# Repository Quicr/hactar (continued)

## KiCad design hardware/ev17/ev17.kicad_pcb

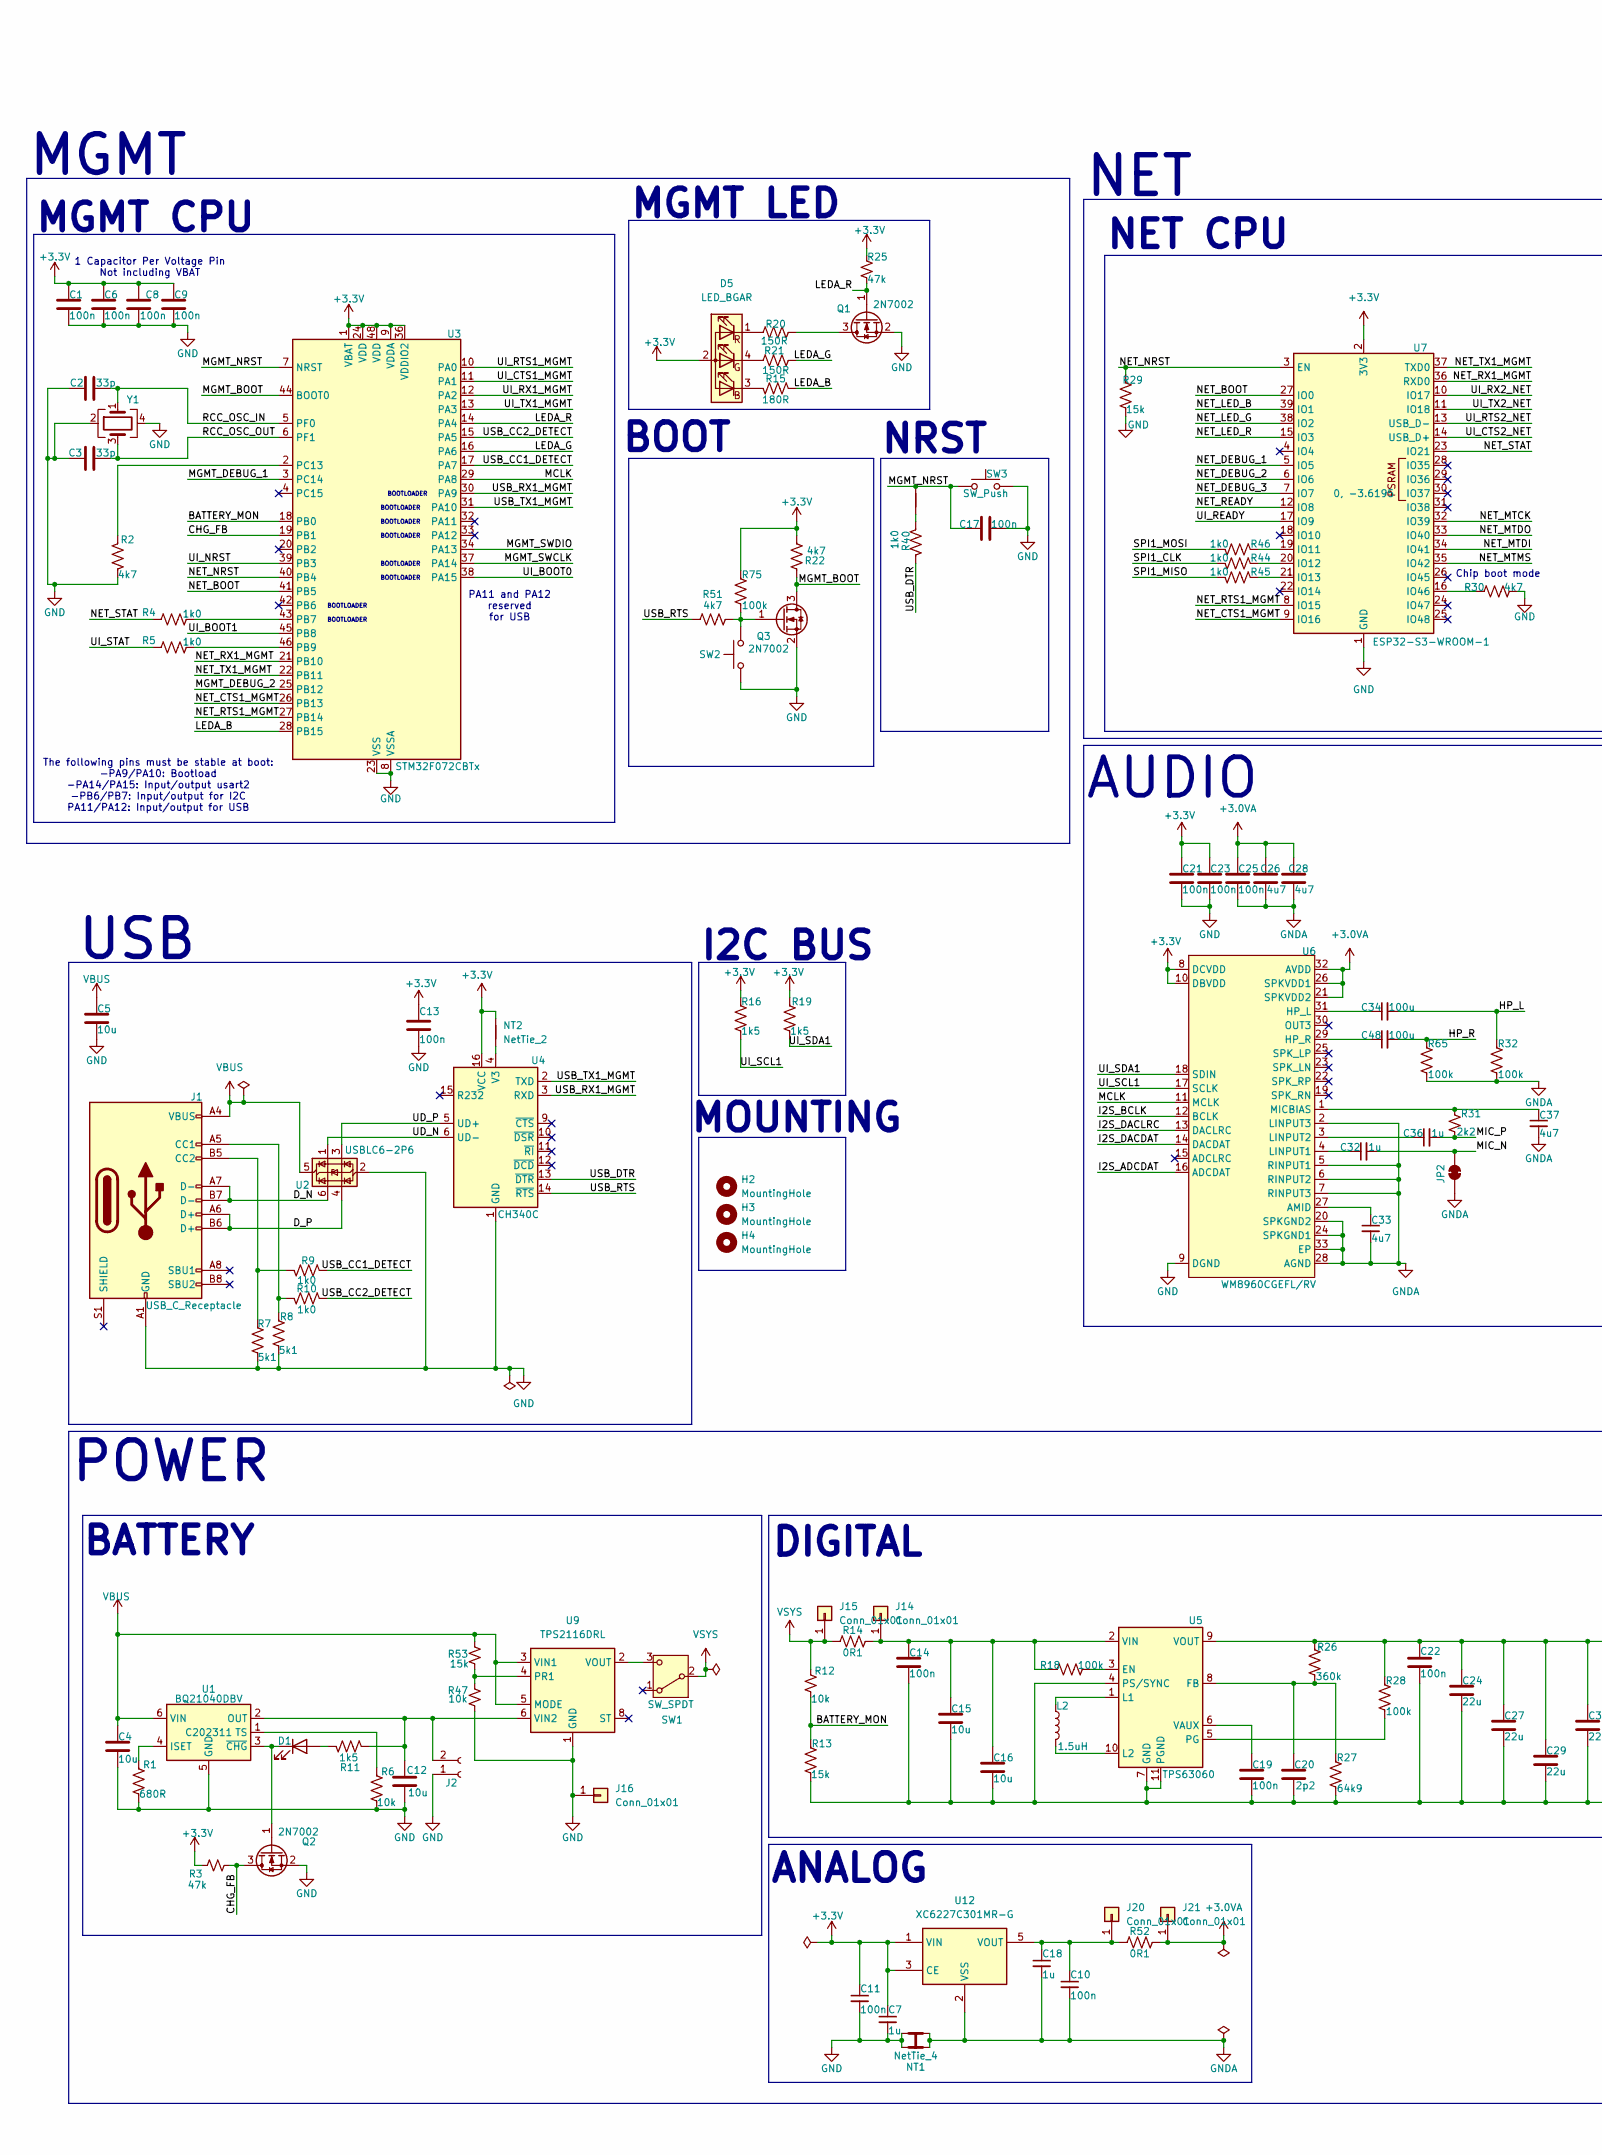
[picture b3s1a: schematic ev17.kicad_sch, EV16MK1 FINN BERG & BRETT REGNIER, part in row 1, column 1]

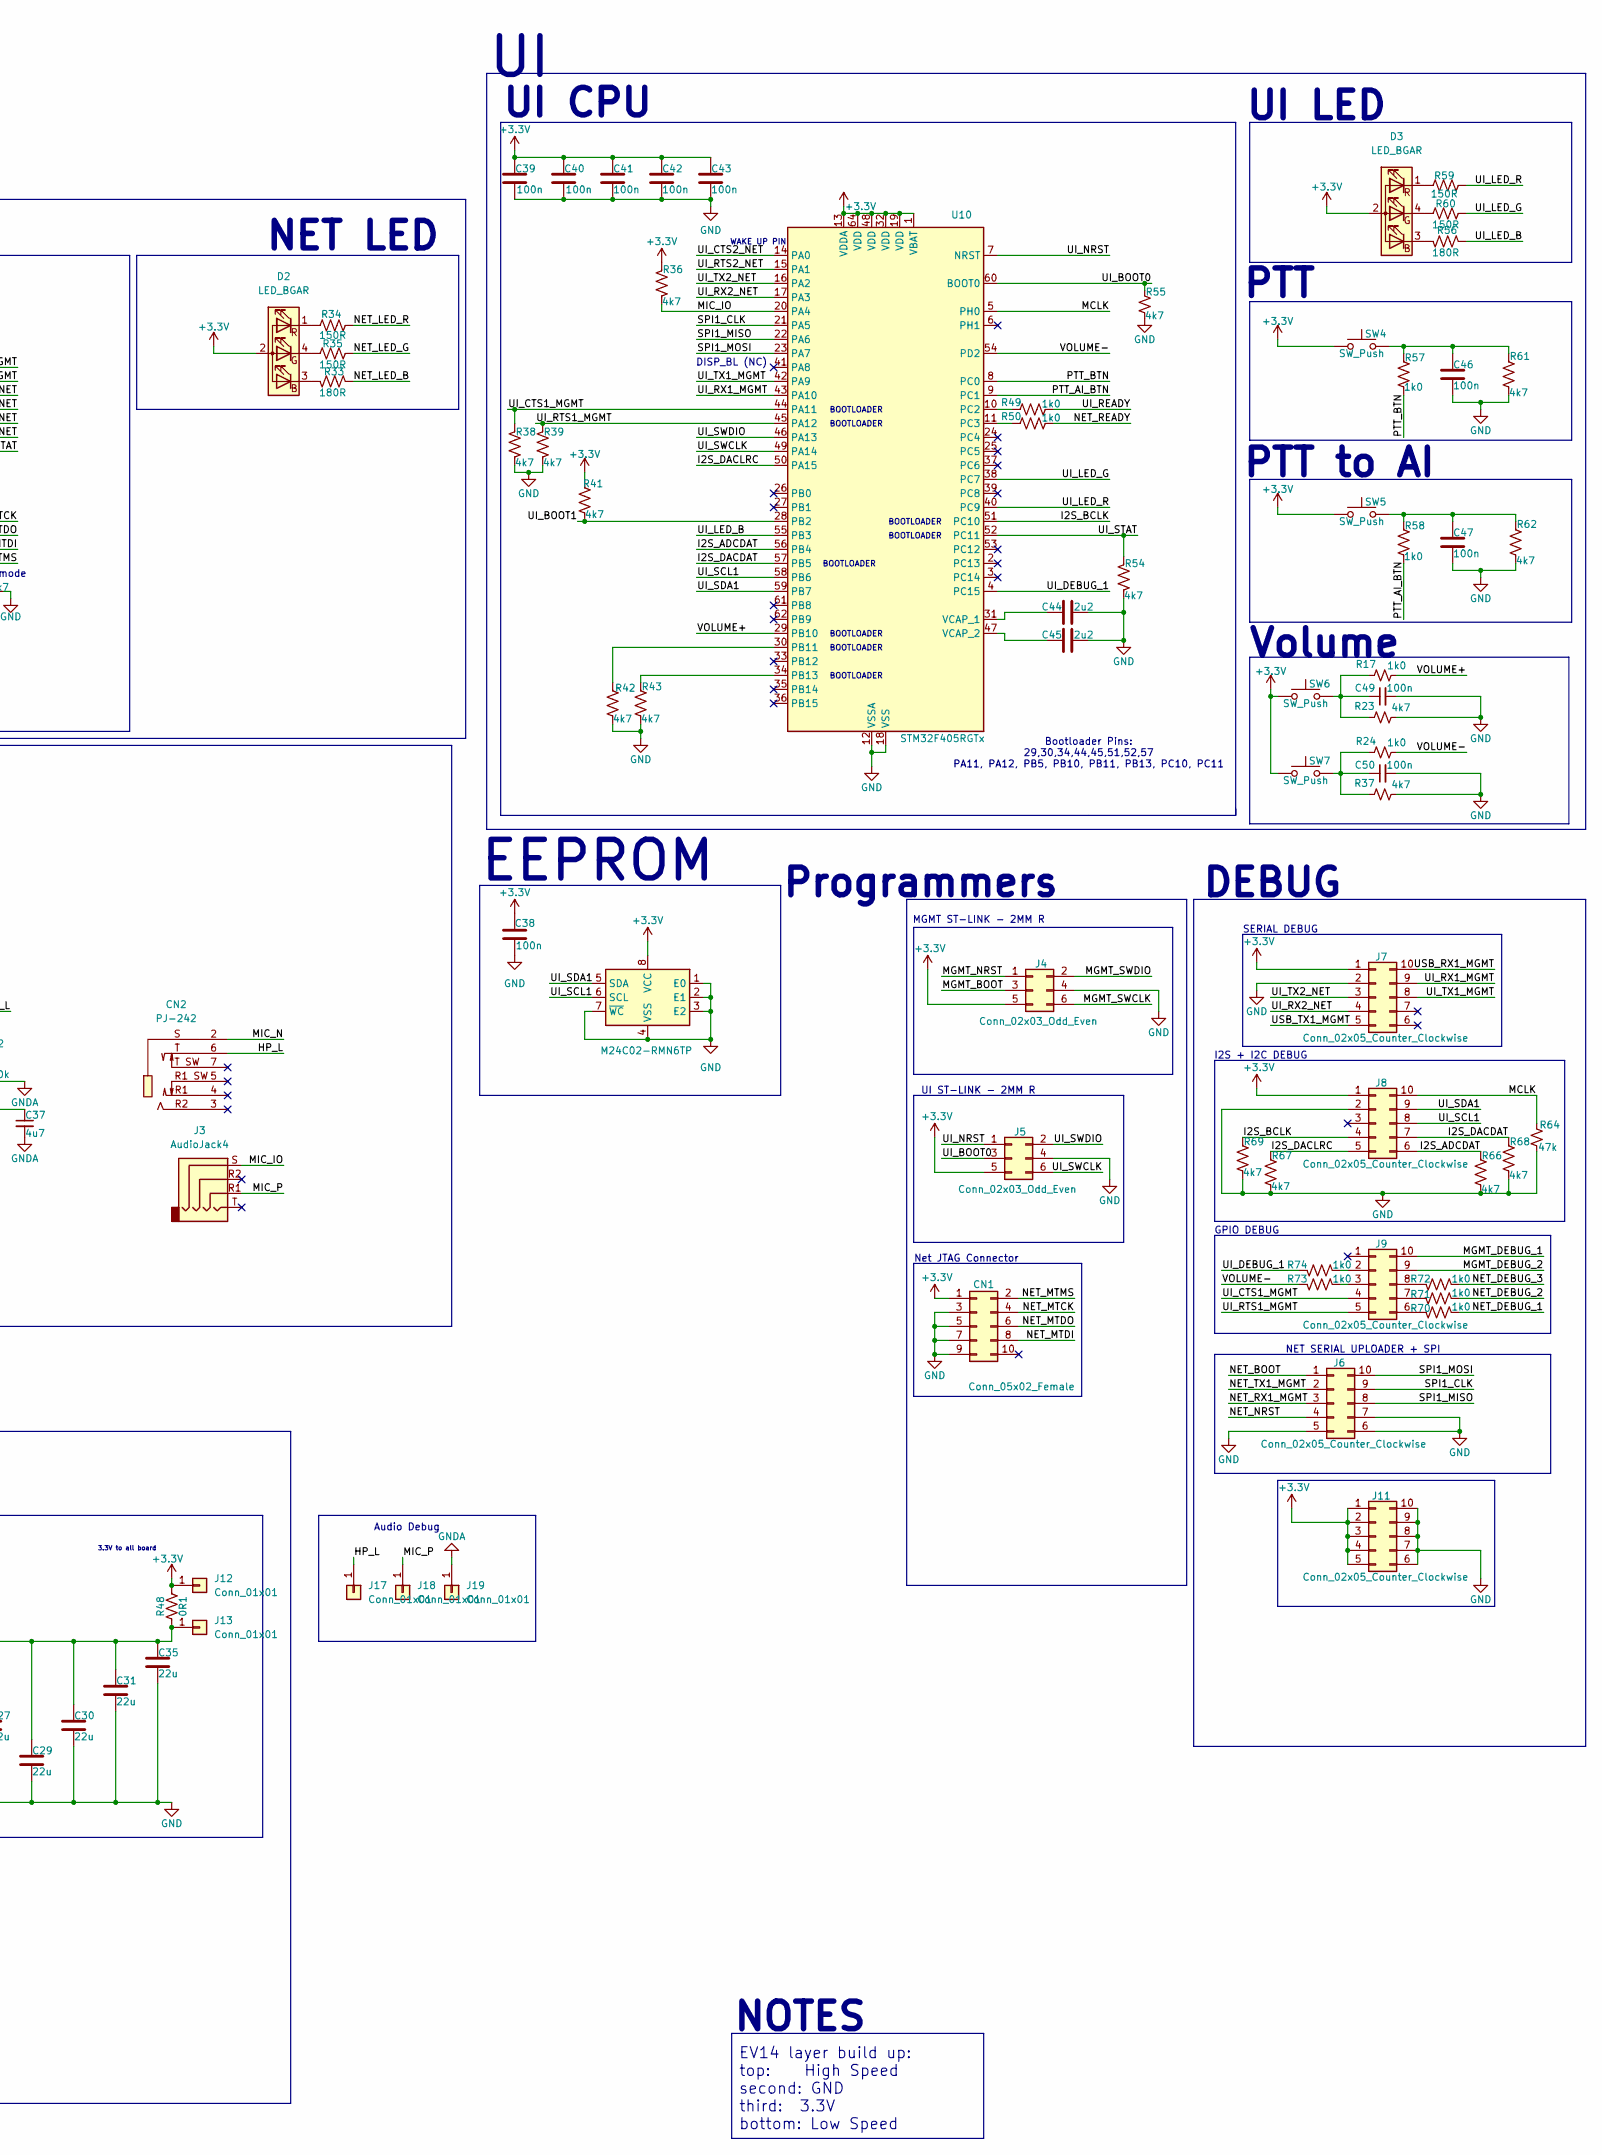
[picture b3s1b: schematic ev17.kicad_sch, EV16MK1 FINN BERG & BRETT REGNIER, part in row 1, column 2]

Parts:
C1, C6, C8, C9, C13, C17, C21, C23, C25, C38, C39, C40, C41, C42, C43, C46, C47, C49, C50: 100n; C_0402_1005Metric; JLCPCB Part # C1525
C2, C3: 33p; C_0805_2012Metric; JLCPCB Part # C107115
C4, C5, C12: 10u; C_0402_1005Metric; JLCPCB Part # C307415
C7, C18, C32, C36: 1u; C_0402_1005Metric; JLCPCB Part # C52923
C10, C11, C14, C19, C22: 100n; C_0805_2012Metric; JLCPCB Part # C85866
C15, C16: 10u; C_0805_2012Metric; JLCPCB Part # C17024
C20: 2p2; C_0805_2012Metric; JLCPCB Part # C519933
C24, C27, C29, C30, C31, C35: 22u; C_0805_2012Metric; JLCPCB Part # C5674
C26, C28, C33, C37: 4u7; C_0402_1005Metric; JLCPCB Part # C23733
C34, C48: 100u; C_1206_3216Metric; JLCPCB Part # C15008
C44, C45: 2u2; C_0402_1005Metric; JLCPCB Part # C12530
CN1: Conn_05x02_Female; IDC-SMD_10P-P1.27_X1270WVS-2X05B-6TV01; JLCPCB Part # C2962222
CN2: PJ-242; AUDIO-SMD_PJ-242D-SMT; JLCPCB Part # C431536
D1: LED; D_0805_2012Metric; JLCPCB Part # C130114
D2, D3, D5: LED_BGAR; LED-ARRAY-SMD_4P-L1.6-W1.5-TL_NH-B1515RGBA; JLCPCB Part # C2874115
H2, H3, H4: MountingHole; MountingHole_2.7mm_M2.5
J1: USB_C_Receptacle; USB-C_SMD-TYPE-C-31-M-12; JLCPCB Part # C165948
J2: Conn_01x02_Socket; JST_PH_S2B-PH-SM4-TB_1x02-1MP_P2.00mm_Horizontal; JLCPCB Part # C295747
J3: AudioJack4; AUDIO-SMD_PJ-320D; JLCPCB Part # C431535
J4, J5: Conn_02x03_Odd_Even; HDR-SMD_6P-P2.54-V-M-R2-C3-LS7.5-2; JLCPCB Part # C3294461
J6, J7, J8, J9, J11: Conn_02x05_Counter_Clockwise; HDR-SMD_10P-P2.54-V-F-R2-C5-LS7.1-1; JLCPCB Part # C3975150
J12, J13, J14, J15, J16, J17, J18, J19, J20, J21: Conn_01x01; PinSocket_1x01_P2.00mm_Vertical; JLCPCB Part # C2882984
JP2: SolderJumper_2_Bridged; NetTie-2_SMD_Pad0.5mm
L2: 1.5uH; L_Coilcraft_XxL4020; JLCPCB Part # C3033018
NT1: NetTie_4; NetTie-4_SMD_Pad0.5mm
NT2, NT3: NetTie_2; NetTie-2_SMD_Pad0.5mm
Q1, Q2, Q3: 2N7002; SOT-23; JLCPCB Part # C8545
R1: 680R; R_0402_1005Metric; JLCPCB Part # C25130
R2, R22, R23, R30, R36, R37, R38, R39, R41, R42, R43, R51, R54, R55, R61, R62, R66, R67, R68, R69: 4k7; R_0402_1005Metric; JLCPCB Part # C25900
R3, R25, R64: 47k; R_0402_1005Metric; JLCPCB Part # C25792
R4, R5, R9, R10, R17, R24, R40, R44, R45, R46, R49, R50, R57, R58, R70, R71, R72, R73, R74: 1k0; R_0402_1005Metric; JLCPCB Part # C11702
R6, R12, R47: 10k; R_0402_1005Metric; JLCPCB Part # C25744
R7, R8: 5k1; R_0402_1005Metric; JLCPCB Part # C25905
R11, R16, R19: 1k5; R_0402_1005Metric; JLCPCB Part # C25867
R13, R29, R53: 15k; R_0402_1005Metric; JLCPCB Part # C25756
R14, R48, R52: 0R1; R_0603_1608Metric; JLCPCB Part # C111027
R15, R33, R56: 180R; R_0402_1005Metric; JLCPCB Part # C25087
R18, R28, R32, R65, R75: 100k; R_0402_1005Metric; JLCPCB Part # C25741
R20, R21, R34, R35, R59, R60: 150R; R_0402_1005Metric; JLCPCB Part # C25082
R26: 360k; R_0402_1005Metric; JLCPCB Part # C45956
R27: 64k9; R_0402_1005Metric; JLCPCB Part # C26984
R31: 2k2; R_0402_1005Metric; JLCPCB Part # C25879
SW1: SW_SPDT; SW-TH_SS-12D11G5R; JLCPCB Part # C388633
SW2, SW3: SW_Push; KEY-SMD_4P-L4.2-W3.2-P2.20-LS4.6; JLCPCB Part # C139797
SW4, SW5: SW_Push; SW-SMD_4P-L5.1-W5.1-P3.70-LS6.5-TL_H1.5; JLCPCB Part # C318886
SW6, SW7: SW_Push; SW-SMD_SHOU_TS36CA-0.6; JLCPCB Part # C2906288
U1: BQ21040DBV; SOT-23-6; JLCPCB Part # C202311
U2: USBLC6-2P6; SOT-666; JLCPCB Part # C2827693
U3: STM32F072CBTx; LQFP-48_7x7mm_P0.5mm; JLCPCB Part # C80488
U4: CH340C; SOIC-16_3.9x9.9mm_P1.27mm; JLCPCB Part # C84681
U5: TPS63060; Texas_S-PWSON-N10_ThermalVias; JLCPCB Part # C48567
U6: WM8960CGEFL/RV; QFN-32-1EP_5x5mm_P0.5mm_EP3.45x3.45mm_ThermalVias; JLCPCB Part # C18752
U7: ESP32-S3-WROOM-1; JLCPCB Part # C2913204
U8: M24C02-RMN6TP; SOIC-8_3.9x4.9mm_P1.27mm; JLCPCB Part # C83836
U9: TPS2116DRL; SOT-583-8; JLCPCB Part # C3235557
U10: STM32F405RGTx; LQFP-64_10x10mm_P0.5mm; JLCPCB Part # C15742
U12: XC6227C301MR-G; SOT-23-5; JLCPCB Part # C484285
Y1: Crystal_GND24; Crystal_SMD_3225-4Pin_3.2x2.5mm; JLCPCB Part # C13738

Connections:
/Analog_Sense: C10.1, C18.1, J20.1, R52.1, U12.5 (VOUT); also elsewhere on the board
/BATTERY_MON: R12.1, R13.1, U3.18 (PB0)
/BB_Vin_Sense: C14.1, C15.1, C16.1, R14.2, R18.1, U5.2 (VIN); also elsewhere on the board
/BB_Vout_Sense: C22.1, C24.1, C27.1, C29.1, C30.1, C31.1, C35.1, R26.2, R28.2, R48.1, U5.9 (VOUT); also elsewhere on the board
/CHG_FB: Q2.3 (D), R3.1, U3.19 (PB1)
/D_N: J1.A7 (D-), J1.B7 (D-), U2.6 (I/O1)
/D_P: J1.A6 (D+), J1.B6 (D+), U2.4 (I/O2)
/HP_L: C34.2, CN2.6, J17.1, R32.2
/I2S_ADCDAT: J8.6, R66.1, U6.16 (ADCDAT), U10.56 (PB4)
/I2S_BCLK: J8.4, R69.1, U6.12 (BCLK), U10.51 (PC10)
/I2S_DACDAT: J8.7, R68.1, U6.14 (DACDAT), U10.57 (PB5)
/I2S_DACLRC: J8.5, R67.1, U6.13 (DACLRC), U10.50 (PA15)
/LEDA_B: R15.2, U3.28 (PB15)
/LEDA_G: R21.2, U3.16 (PA6)
/LEDA_R: Q1.1 (G), R25.1, U3.14 (PA4)
/MCLK: J8.10, R64.1, U3.29 (PA8), U6.11 (MCLK), U10.5 (PH0)
/MGMT_BOOT: J4.3, Q3.3 (D), R22.1, U3.44 (BOOT0)
/MGMT_DEBUG_1: J9.10, U3.3 (PC14)
/MGMT_DEBUG_2: J9.9, U3.25 (PB12)
/MGMT_NRST: C17.1, J4.1, NT3.2, SW3.1, SW3.2, U3.7 (NRST)
/MGMT_SWCLK: J4.6, U3.37 (PA14)
/MGMT_SWDIO: J4.2, U3.34 (PA13)
/MIC_N: C32.2, CN2.2, JP2.1 (A)
/MIC_P: C36.2, J3.R1, J18.1, R31.1
/NET_BOOT: J6.1, U3.41 (PB5), U7.27 (IO0)
/NET_CTS1_MGMT: U3.26 (PB13), U7.9 (IO16)
/NET_DEBUG_1: R70.1, U7.5 (IO5)
/NET_DEBUG_2: R71.1, U7.6 (IO6)
/NET_DEBUG_3: R72.1, U7.7 (IO7)
/NET_LED_B: R33.1, U7.39 (IO1)
/NET_LED_G: R35.1, U7.38 (IO2)
/NET_LED_R: R34.1, U7.15 (IO3)
/NET_MTCK: CN1.4, U7.32 (IO39)
/NET_MTDI: CN1.8, U7.34 (IO41)
/NET_MTDO: CN1.6, U7.33 (IO40)
/NET_MTMS: CN1.2, U7.35 (IO42)
/NET_NRST: J6.4, R29.1, U3.40 (PB4), U7.3 (EN)
/NET_READY: R50.1, U7.12 (IO8)
/NET_RTS1_MGMT: U3.27 (PB14), U7.8 (IO15)
/NET_RX1_MGMT: J6.3, U3.21 (PB10), U7.36 (RXD0)
/NET_STAT: R4.2, U7.23 (IO21)
/NET_TX1_MGMT: J6.2, U3.22 (PB11), U7.37 (TXD0)
/PTT_AI_BTN: R58.1, U10.9 (PC1)
/PTT_BTN: R57.1, U10.8 (PC0)
/RCC_OSC_IN: C2.2, U3.5 (PF0), Y1.1
/RCC_OSC_OUT: C3.2, U3.6 (PF1), Y1.3
/SPI1_CLK: J6.9, R44.1, U10.21 (PA5)
/SPI1_MISO: J6.8, R45.1, U10.22 (PA6)
/SPI1_MOSI: J6.10, R46.1, U10.23 (PA7)
/UD_N: U2.1 (I/O1), U4.6 (UD-)
/UD_P: U2.3 (I/O2), U4.5 (UD+)
/UI_BOOT0: J5.3, R55.1, U3.38 (PA15), U10.60 (BOOT0)
/UI_BOOT1: R41.2, U3.45 (PB8), U10.28 (PB2)
/UI_CTS1_MGMT: J9.4, R38.2, U3.11 (PA1), U10.44 (PA11)
/UI_CTS2_NET: U7.14 (USB_D+), U10.14 (PA0)
/UI_DEBUG_1: R74.2, U10.4 (PC15)
/UI_LED_B: R56.1, U10.55 (PB3)
/UI_LED_G: R60.1, U10.38 (PC7)
/UI_LED_R: R59.1, U10.40 (PC9)
/UI_NRST: J5.1, U3.39 (PB3), U10.7 (NRST)
/UI_READY: R49.1, U7.17 (IO9)
/UI_RTS1_MGMT: J9.5, R39.2, U3.10 (PA0), U10.45 (PA12)
/UI_RTS2_NET: U7.13 (USB_D-), U10.15 (PA1)
/UI_RX1_MGMT: J7.9, U3.12 (PA2), U10.43 (PA10)
/UI_RX2_NET: J7.4, U7.10 (IO17), U10.17 (PA3)
/UI_SCL1: J8.8, R16.2, U6.17 (SCLK), U8.6 (SCL), U10.58 (PB6)
/UI_SDA1: J8.9, R19.2, U6.18 (SDIN), U8.5 (SDA), U10.59 (PB7)
/UI_STAT: R5.2, R54.2, U10.52 (PC11)
/UI_SWCLK: J5.6, U10.49 (PA14)
/UI_SWDIO: J5.2, U10.46 (PA13)
/UI_TX1_MGMT: J7.8, U3.13 (PA3), U10.42 (PA9)
/UI_TX2_NET: J7.3, U7.11 (IO18), U10.16 (PA2)
/USB_CC1_DETECT: R9.1, U3.17 (PA7)
/USB_CC2_DETECT: R10.1, U3.15 (PA5)
/USB_DTR: R40.2, U4.13 (~DTR)
/USB_RTS: R51.1, U4.14 (~RTS)
/USB_RX1_MGMT: J7.10, U3.30 (PA9), U4.3 (RXD)
/USB_TX1_MGMT: J7.5, U3.31 (PA10), U4.2 (TXD)
/VOLUME+: R17.1, U10.29 (PB10)
/VOLUME-: R24.1, R73.2, U10.54 (PD2)
GND: C1.1, C2.1, C3.1, C4.2, C5.2, C6.1, C7.2, C8.1, C9.1, C11.2, C12.2, C13.2, C14.2, C15.2, C16.2, C17.2, C19.2, C20.2, C21.1, C22.2, C23.1, C24.2, C27.2, C29.2, C30.2, C31.2, C35.2, C38.1, C39.2, C40.2, C41.2, C42.2, C43.2, C44.1, C45.1, C46.2, C47.2, C49.2, C50.2, CN1.3, CN1.5, CN1.7, CN1.9, J1.A1 (GND), J1.A12 (GND), J1.B1 (GND), J1.B12 (GND), J2.1, J4.4, J5.4, J6.5, J6.6, J6.7, J7.2, J8.2, J11.6, J11.7, J11.8, J11.9, J11.10, NT1.1, NT1.3, Q1.2 (S), Q2.2 (S), Q3.2 (S), R1.2, R2.1, R6.2, R7.1, R8.1, R13.2, R23.1, R27.1, R29.2, R30.2, R37.1, R38.1, R39.1, R42.1, R43.1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; also elsewhere on the board
GNDA: C10.2, C18.2, C25.1, C26.2, C28.2, C33.2, C37.2, J19.1, JP2.2 (B), NT1.2, NT1.4, R32.1, R65.1, U6.2 (LINPUT3), U6.5 (RINPUT1), U6.6 (RINPUT2), U6.7 (RINPUT3), U6.20 (SPKGND2), U6.24 (SPKGND1), U6.28 (AGND), U6.33 (EP), U12.2 (VSS); also elsewhere on the board
unnamed: C46.1, R57.2, R61.2, SW4.3, SW4.4
unnamed: C47.1, R58.2, R62.2, SW5.3, SW5.4
unnamed: C48.1, U6.29 (HP_R)
unnamed: C48.2, R65.2
unnamed: C49.1, R17.2, R23.2, SW6.2
unnamed: C50.1, R24.2, R37.2, SW7.2
unnamed: D1.2 (A), R11.2
unnamed: D1.1 (K), Q2.1 (G), U1.3 (~CHG)
unnamed: D2.3 (BK), R33.2
unnamed: D2.4 (GK), R35.2
unnamed: D2.1 (RK), R34.2
unnamed: D3.3 (BK), R56.2
unnamed: D3.4 (GK), R60.2
unnamed: D3.1 (RK), R59.2
unnamed: D5.3 (BK), R15.1
unnamed: D5.4 (GK), R21.1
unnamed: D5.1 (RK), R20.1
unnamed: J1.A5 (CC1), R8.2, R10.2
unnamed: J1.B5 (CC2), R7.2, R9.2
unnamed: C12.1, J2.2, R11.1, U1.2 (OUT), U9.6 (VIN2)
unnamed: J9.2, R74.1
unnamed: J9.3, R73.1
unnamed: J9.6, R70.2
unnamed: J9.7, R71.2
unnamed: J9.8, R72.2
unnamed: NT3.1, R40.1
unnamed: Q1.3 (D), R20.2
unnamed: Q3.1 (G), R51.2, R75.1, SW2.3, SW2.4
unnamed: SW1.3 (C), U9.2 (VOUT), U9.7 (VOUT)
unnamed: R1.1, U1.4 (ISET)
unnamed: R6.1, U1.1 (TS)
unnamed: R4.1, U3.43 (PB7)
unnamed: R5.1, U3.46 (PB9)
unnamed: R2.2, U3.2 (PC13)
unnamed: NT2.1, U4.4 (V3)
unnamed: R18.2, U5.3 (EN)
unnamed: C20.1, R26.1, R27.2, U5.8 (FB)
unnamed: L2.1, U5.1 (L1)
unnamed: L2.2, U5.10 (L2)
unnamed: R28.1, U5.5 (PG)
unnamed: C19.1, U5.6 (VAUX)
unnamed: C33.1, U6.27 (AMID)
unnamed: C34.1, U6.31 (HP_L)
unnamed: C32.1, U6.4 (LINPUT1)
unnamed: C36.1, U6.3 (LINPUT2)
unnamed: C37.1, R31.2, U6.1 (MICBIAS)
unnamed: R46.2, U7.19 (IO11)
unnamed: R44.2, U7.20 (IO12)
unnamed: R45.2, U7.21 (IO13)
unnamed: R30.1, U7.16 (IO46)
unnamed: R47.2, R53.1, U9.4 (PR1)
unnamed: R42.2, U10.30 (PB11)
unnamed: R43.2, U10.34 (PB13)
unnamed: R49.2, U10.10 (PC2)
unnamed: R50.2, U10.11 (PC3)
unnamed: C44.2, U10.31 (VCAP_1)
unnamed: C45.2, U10.47 (VCAP_2)
VBUS: C4.1, C5.1, J1.A4 (VBUS), J1.A9 (VBUS), J1.B4 (VBUS), J1.B9 (VBUS), R53.2, U1.6 (VIN), U2.5 (VBUS), U9.3 (VIN1), U9.5 (MODE)
VSYS: J15.1, R12.2, R14.1, SW1.2 (B); also elsewhere on the board

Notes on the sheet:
MGMT
BOOTLOADER
Audio Debug
NET CPU
MGMT CPU
WAKE UP PIN
DISP_BL (NC)
PTT to AI
NET
POWER
Programmers
MOUNTING
BATTERY
NET LED
UI CPU
Bootloader Pins: 29,30,34,44,45,51,52,57 PA11, PA12, PB5, PB10, PB11, PB13, PC10, PC11
UI ST-LINK - 2MM R
Chip boot mode
Net JTAG Connector
NRST
The following pins must be stable at boot: -PA9/PA10: Bootload -PA14/PA15: Input/output usart2 -PB6/PB7: Input/output for I2C PA11/PA12: Input/output for USB
DIGITAL
Volume
EV14 layer build up: top: High Speed second: GND third: 3.3V bottom: Low Speed
NET SERIAL UPLOADER + SPI
AUDIO
PTT
BOOT
PA11 and PA12 reserved for USB
EEPROM
I2C BUS
USB
MGMT LED
3.3V to all board
DEBUG
NOTES
MGMT ST-LINK - 2MM R
GPIO DEBUG
SERIAL DEBUG
1 Capacitor Per Voltage Pin Not including VBAT

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
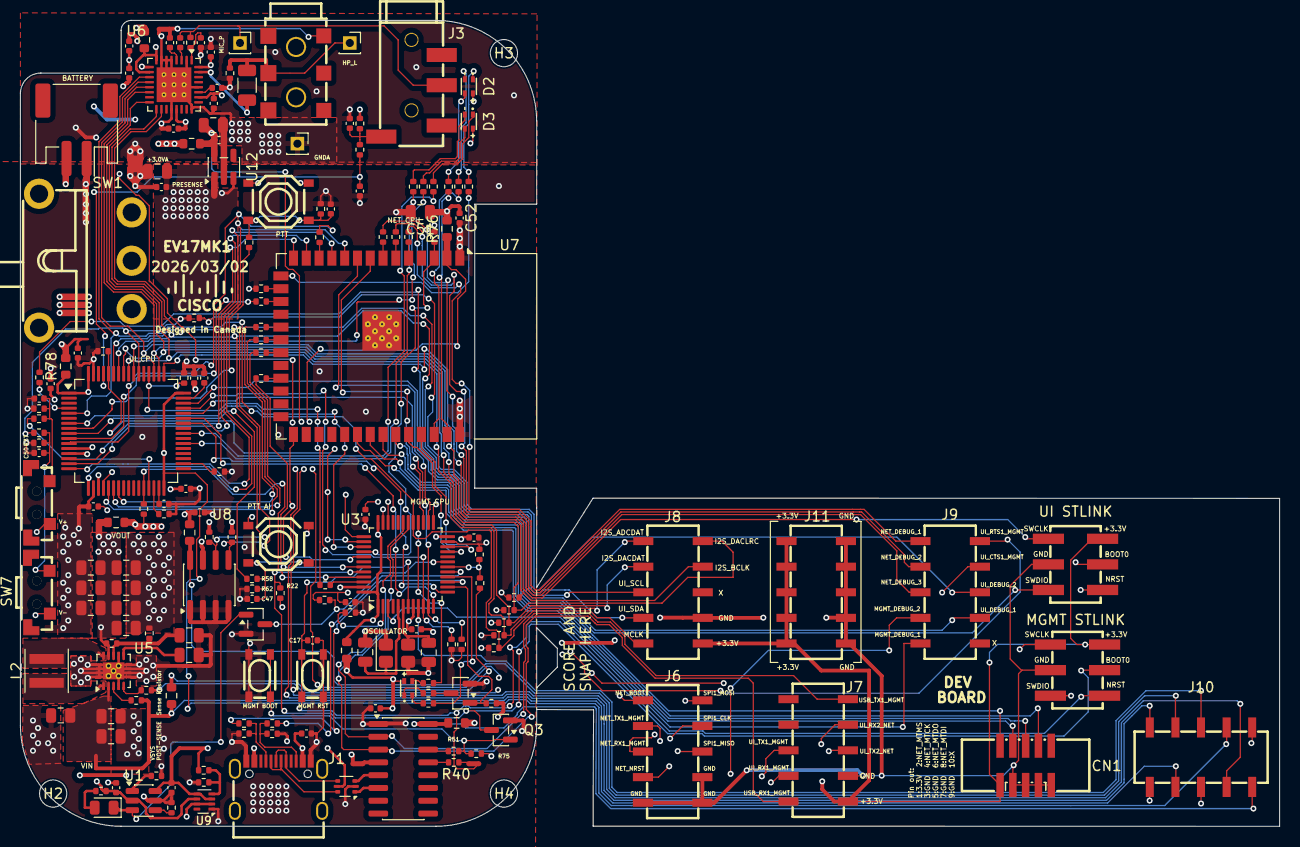
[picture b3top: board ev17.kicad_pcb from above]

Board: 4 copper layers, 125.0 x 80.0 mm, 183 parts (0 on the bottom side), 149 nets.

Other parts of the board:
C51: 10u; C_0805_2012Metric
C52: 100n; C_0402_1005Metric
C53: 150n; C_0402_1005Metric
C54: 220n; C_0402_1005Metric
J10: Conn_02x05_Counter_Clockwise; HDR-SMD_10P-P2.54-V-F-R2-C5-LS7.1-1
R63, R76, R77, R78, R79, R80: 0R1; R_0603_1608Metric
R81: 10k; R_0402_1005Metric

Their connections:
/Analog_Sense: J10.4; also elsewhere on the board
/BB_Vin_Sense: J10.2; also elsewhere on the board
/BB_Vout_Sense: J10.3; also elsewhere on the board
GND: C51.2, C52.2, C53.2; also elsewhere on the board
GNDA: C54.2; also elsewhere on the board
VSYS: J10.1; also elsewhere on the board

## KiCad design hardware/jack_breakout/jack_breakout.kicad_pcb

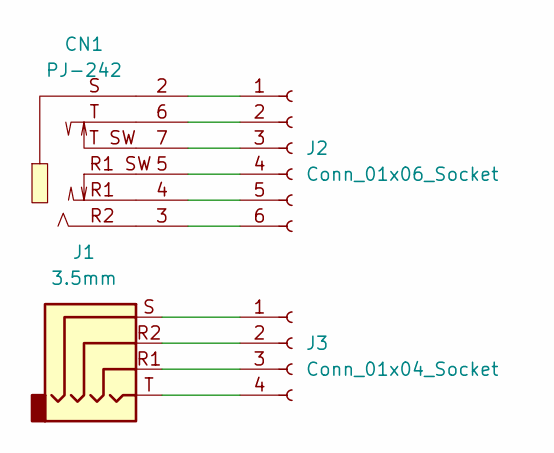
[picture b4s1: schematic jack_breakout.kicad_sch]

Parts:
CN1: PJ-242; AUDIO-SMD_PJ-242D-SMT; LCSC Part C431536
J1: 3.5mm; AUDIO-SMD_PJ-320D
J2: Conn_01x06_Socket; PinSocket_1x06_P2.54mm_Vertical
J3: Conn_01x04_Socket; PinSocket_1x04_P2.54mm_Vertical

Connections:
unnamed: CN1.2, J2.1
unnamed: CN1.6, J2.2
unnamed: CN1.7, J2.3
unnamed: CN1.5, J2.4
unnamed: CN1.4, J2.5
unnamed: CN1.3, J2.6
unnamed: J1.S, J3.1
unnamed: J1.R2, J3.2
unnamed: J1.R1, J3.3
unnamed: J1.T, J3.4

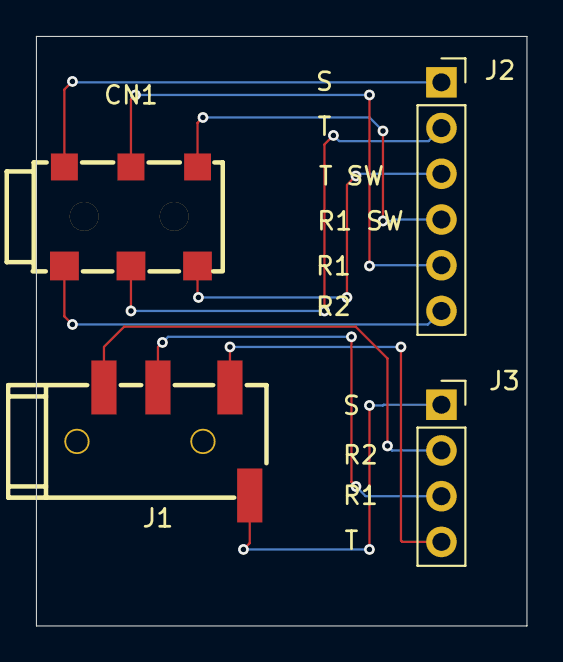
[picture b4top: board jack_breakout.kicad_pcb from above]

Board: 2 copper layers, 27.2 x 32.8 mm, 4 parts (0 on the bottom side), 10 nets.

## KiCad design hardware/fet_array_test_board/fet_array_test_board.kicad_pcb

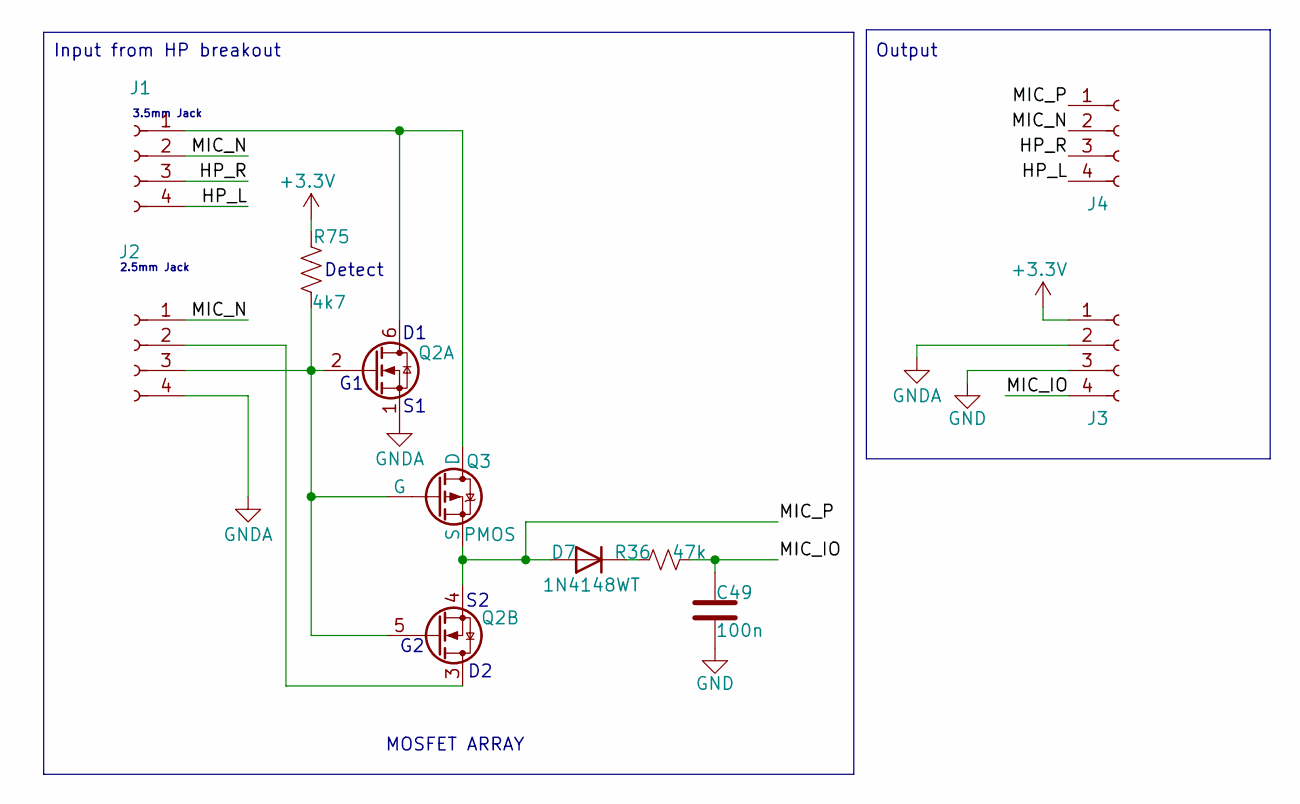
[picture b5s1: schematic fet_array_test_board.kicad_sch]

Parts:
C49: 100n; C_0402_1005Metric; JLCPCB Part # C1525
D7: 1N4148WT; D_SOD-523; JLCPCB Part # C27748
J1, J2, J3, J4: Conn_01x04_Socket; PinHeader_1x04_P2.54mm_Vertical_SMD_Pin1Right; JLCPCB Part # C42379197
Q2: Q_Dual_NMOS_S1G1D2S2G2D1; SOT-363_L2.1-W1.3-P0.65-LS2.3-BL; JLCPCB Part # C5362112
Q3: PMOS; SOT-23-3_L2.9-W1.3-P1.90-LS2.4-BR; JLCPCB Part # C181091
R36: 47k; R_0402_1005Metric; JLCPCB Part # C25792
R75: 4k7; R_0402_1005Metric; JLCPCB Part # C25900

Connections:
+3.3V: J3.1, R75.2
/HP_L: J1.4, J4.4
/HP_R: J1.3, J4.3
/MIC_IO: C49.1, J3.4, R36.1
/MIC_N: J1.2, J2.1, J4.2
/MIC_P: D7.2 (A), J4.1, Q2.4 (S), Q3.3 (S)
GND: C49.2, J3.3
GNDA: J2.4, J3.2, Q2.1 (S)
unnamed: D7.1 (K), R36.2
unnamed: J1.1, Q2.6 (D), Q3.1 (D)
unnamed: J2.2, Q2.3 (D)
unnamed: J2.3, Q2.2 (G), Q2.5 (G), Q3.2 (G), R75.1

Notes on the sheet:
Input from HP breakout
2.5mm Jack
MOSFET ARRAY
Output
3.5mm Jack
Detect

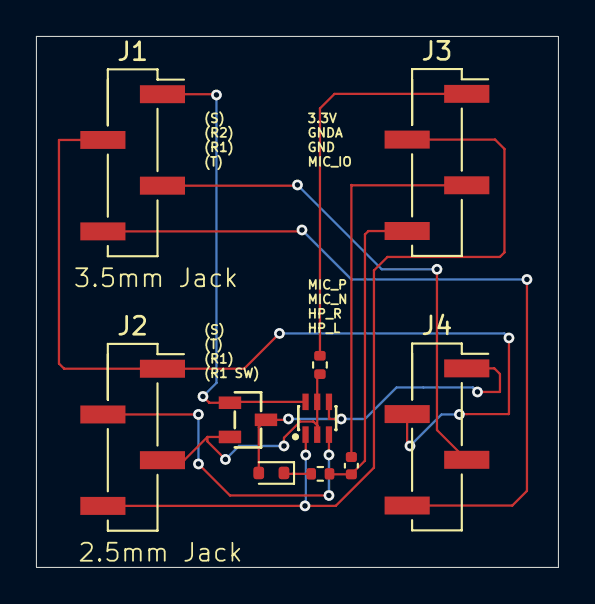
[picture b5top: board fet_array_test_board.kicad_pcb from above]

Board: 2 copper layers, 29.0 x 29.5 mm, 10 parts (0 on the bottom side), 12 nets.

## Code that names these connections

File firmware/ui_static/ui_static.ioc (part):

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Mcu.Name=STM32F405RGTx
Mcu.Package=LQFP64
Mcu.UserName=STM32F405RGTx
PA1.GPIOParameters=GPIO_Label
PA1.GPIO_Label=UI_LED_B
PA1.Signal=GPIO_Output
PA10.GPIOParameters=GPIO_Label
PA10.GPIO_Label=UI_RX1_MGMT
PA10.Mode=Asynchronous
PA10.Signal=USART1_RX
PA11.GPIOParameters=GPIO_Label
PA11.GPIO_Label=UI_DEBUG_1
PA11.Signal=GPIO_Output
PA12.GPIOParameters=GPIO_Label
PA12.GPIO_Label=UI_DEBUG_2
PA12.Signal=GPIO_Output
PA13.Signal=SYS_JTMS-SWDIO
PA14.Signal=SYS_JTCK-SWCLK
PA15.GPIOParameters=GPIO_Label
PA15.GPIO_Label=I2S_DACLRC
PA15.Mode=Full_Duplex_Slave
PA15.Signal=I2S3_WS
PA2.GPIOParameters=GPIO_Label
PA2.GPIO_Label=UI_TX2_NET
PA2.Mode=Asynchronous
PA2.Signal=USART2_TX
PA3.GPIOParameters=GPIO_Label
PA3.GPIO_Label=UI_RX2_NET
PA3.Mode=Asynchronous
PA3.Signal=USART2_RX
PA4.GPIOParameters=GPIO_Label
PA4.GPIO_Label=UI_DEBUG_3
PA4.Signal=GPIO_Output
PA5.GPIOParameters=GPIO_Label
PA5.GPIO_Label=SPI1_CLK
PA5.Mode=Simplex_Bidirectional_Master
PA5.Signal=SPI1_SCK
PA6.GPIOParameters=GPIO_Label
PA6.GPIO_Label=UI_LED_R
PA6.Signal=GPIO_Output
PA7.GPIOParameters=GPIO_Label
PA7.GPIO_Label=SPI1_MOSI
PA7.Mode=Simplex_Bidirectional_Master
PA7.Signal=SPI1_MOSI
PA8.GPIOParameters=GPIO_Label
PA8.GPIO_Label=KB_ROW4
PA8.Signal=GPIO_Input
PA9.GPIOParameters=GPIO_Label
PA9.GPIO_Label=UI_TX1_MGMT
PA9.Mode=Asynchronous
PA9.Signal=USART1_TX
PB0.GPIOParameters=GPIO_Label
PB0.GPIO_Label=KB_ROW5
PB0.Signal=GPIO_Input
PB1.GPIOParameters=GPIO_Label
PB1.GPIO_Label=KB_ROW6
PB1.Signal=GPIO_Input
PB10.GPIOParameters=GPIO_Label
PB10.GPIO_Label=KB_LED
PB10.Signal=GPIO_Output
PB11.GPIOParameters=GPIO_Label
PB11.GPIO_Label=KB_ROW7
PB11.Signal=GPIO_Input
PB12.GPIOParameters=GPIO_Label
PB12.GPIO_Label=KB_ROW1
PB12.Signal=GPIO_Input
PB13.GPIOParameters=GPIO_Label
PB13.GPIO_Label=KB_COL1
PB13.Signal=GPIO_Output
PB14.GPIOParameters=GPIO_Label
PB14.GPIO_Label=KB_ROW2
PB14.Signal=GPIO_Input
PB15.GPIOParameters=GPIO_Label
PB15.GPIO_Label=KB_COL2
PB15.Signal=GPIO_Output
PB2.GPIOParameters=GPIO_Label
PB2.GPIO_Label=UI_BOOT1
PB2.Signal=GPIO_Input
PB4.GPIOParameters=GPIO_Label
PB4.GPIO_Label=I2S_ADCDAT
PB4.Mode=Full_Duplex_Slave
PB4.Signal=I2S3_ext_SD
PB5.GPIOParameters=GPIO_Label
PB5.GPIO_Label=I2S_DACDAT
PB5.Mode=Full_Duplex_Slave
PB5.Signal=I2S3_SD
PB6.Mode=I2C
PB6.Signal=I2C1_SCL
PB7.Mode=I2C
PB7.Signal=I2C1_SDA
PB8.GPIOParameters=GPIO_Label
PB8.GPIO_Label=DISP_CS
PB8.Signal=GPIO_Output
PB9.GPIOParameters=GPIO_Label
PB9.GPIO_Label=DISP_DC
PB9.Signal=GPIO_Output
PC0.GPIOParameters=GPIO_PuPd,GPIO_Label
PC0.GPIO_Label=PTT_BTN
PC0.GPIO_PuPd=GPIO_PULLUP
PC0.Signal=GPIO_Input
PC1.GPIOParameters=GPIO_PuPd,GPIO_Label
PC1.GPIO_Label=PTT_AI_BTN
PC1.GPIO_PuPd=GPIO_PULLUP
PC1.Signal=GPIO_Input
PC10.GPIOParameters=GPIO_Label
PC10.GPIO_Label=I2S_BCLK
PC10.Mode=Full_Duplex_Slave
PC10.Signal=I2S3_CK
PC11.GPIOParameters=GPIO_Label
PC11.GPIO_Label=UI_STAT
PC11.Signal=GPIO_Input
PC13-ANTI_TAMP.GPIOParameters=GPIO_Label
PC13-ANTI_TAMP.GPIO_Label=DISP_RST
PC13-ANTI_TAMP.Signal=GPIO_Output
PC14-OSC32_IN.GPIOParameters=GPIO_Label
PC14-OSC32_IN.GPIO_Label=DISP_BL
PC14-OSC32_IN.Signal=GPIO_Output
PC2.GPIOParameters=GPIO_Label
PC2.GPIO_Label=USB_CC2_DETECT
PC2.Signal=ADCx_IN12
PC3.GPIOParameters=GPIO_Label
PC3.GPIO_Label=USB_CC1_DETECT
PC3.Signal=ADCx_IN13
PC4.GPIOParameters=GPIO_Label
PC4.GPIO_Label=BATTERY_MON
PC4.Signal=ADCx_IN14
PC5.GPIOParameters=GPIO_Label
PC5.GPIO_Label=UI_LED_G
PC5.Signal=GPIO_Output
PC6.GPIOParameters=GPIO_Label
PC6.GPIO_Label=KB_COL3
PC6.Signal=GPIO_Output
PC7.GPIOParameters=GPIO_Label
PC7.GPIO_Label=KB_COL4
PC7.Signal=GPIO_Output
PC8.GPIOParameters=GPIO_Label
PC8.GPIO_Label=KB_ROW3
PC8.Signal=GPIO_Input
PC9.GPIOParameters=GPIO_Label
PC9.GPIO_Label=KB_COL5
PC9.Signal=GPIO_Output
PH0-OSC_IN.GPIOParameters=GPIO_Label
PH0-OSC_IN.GPIO_Label=MCLK
PH0-OSC_IN.Mode=HSE-External-Clock-Source
PH0-OSC_IN.Signal=RCC_OSC_IN
PH1-OSC_OUT.GPIOParameters=GPIO_Label
PH1-OSC_OUT.GPIO_Label=NC
PH1-OSC_OUT.Mode=HSE-External-Clock-Source
PH1-OSC_OUT.Signal=RCC_OSC_OUT
RCC.HSE_VALUE=24000000
RCC.SYSCLKFreq_VALUE=168000000
RCC.SYSCLKSource=RCC_SYSCLKSOURCE_PLLCLK
board=custom

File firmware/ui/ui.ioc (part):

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Mcu.Name=STM32F405RGTx
Mcu.Package=LQFP64
Mcu.UserName=STM32F405RGTx
PA10.GPIOParameters=GPIO_Label
PA10.GPIO_Label=UI_RX1_MGMT
PA10.Mode=Asynchronous
PA10.Signal=USART1_RX
PA13.Mode=Serial_Wire
PA13.Signal=SYS_JTMS-SWDIO
PA14.Mode=Serial_Wire
PA14.Signal=SYS_JTCK-SWCLK
PA15.GPIOParameters=GPIO_Label
PA15.GPIO_Label=I2S_DACLRC
PA15.Mode=Full_Duplex_Slave
PA15.Signal=I2S3_WS
PA2.GPIOParameters=GPIO_Label
PA2.GPIO_Label=UI_TX2_NET
PA2.Mode=Asynchronous
PA2.Signal=USART2_TX
PA3.GPIOParameters=GPIO_PuPd,GPIO_Label
PA3.GPIO_Label=UI_RX2_NET
PA3.GPIO_PuPd=GPIO_PULLDOWN
PA3.Mode=Asynchronous
PA3.Signal=USART2_RX
PA4.GPIOParameters=GPIO_Label
PA4.GPIO_Label=MIC_IO
PA4.Signal=GPIO_Input
PA5.GPIOParameters=GPIO_Label
PA5.GPIO_Label=SPI1_CLK
PA5.Mode=Full_Duplex_Master
PA5.Signal=SPI1_SCK
PA6.Mode=Full_Duplex_Master
PA6.Signal=SPI1_MISO
PA7.GPIOParameters=GPIO_Label
PA7.GPIO_Label=SPI1_MOSI
PA7.Mode=Full_Duplex_Master
PA7.Signal=SPI1_MOSI
PA8.GPIOParameters=GPIO_PuPd,GPIO_Label
PA8.GPIO_Label=DISP_BL
PA8.GPIO_PuPd=GPIO_NOPULL
PA8.Signal=GPIO_Output
PA9.GPIOParameters=GPIO_Label
PA9.GPIO_Label=UI_TX1_MGMT
PA9.Mode=Asynchronous
PA9.Signal=USART1_TX
PB1.GPIOParameters=GPIO_Label
PB1.GPIO_Label=PLUG_DETECT
PB1.Signal=GPIO_Input
PB10.GPIOParameters=GPIO_Label
PB10.GPIO_Label=VOLUME_UP
PB10.Signal=GPIO_Input
PB11.GPIOParameters=GPIO_Label
PB11.GPIO_Label=KB_COL1
PB11.Signal=GPIO_Output
PB12.GPIOParameters=GPIO_Label
PB12.GPIO_Label=KB_COL2
PB12.Signal=GPIO_Output
PB13.GPIOParameters=GPIO_Label
PB13.GPIO_Label=KB_COL3
PB13.Signal=GPIO_Output
PB14.GPIOParameters=GPIO_Label
PB14.GPIO_Label=KB_COL4
PB14.Signal=GPIO_Output
PB15.GPIOParameters=GPIO_PuPd,GPIO_Label
PB15.GPIO_Label=KB_ROW7
PB15.GPIO_PuPd=GPIO_PULLDOWN
PB15.Signal=GPIO_Input
PB2.GPIOParameters=GPIO_Label
PB2.GPIO_Label=UI_BOOT1
PB2.Signal=GPIO_Input
PB3.GPIOParameters=GPIO_Label
PB3.GPIO_Label=DISP_CS
PB3.Signal=GPIO_Output
PB4.GPIOParameters=GPIO_Label
PB4.GPIO_Label=I2S_ADCDAT
PB4.Mode=Full_Duplex_Slave
PB4.Signal=I2S3_ext_SD
PB5.GPIOParameters=GPIO_Label
PB5.GPIO_Label=I2S_DACDAT
PB5.Mode=Full_Duplex_Slave
PB5.Signal=I2S3_SD
PB6.GPIOParameters=GPIO_Label
PB6.GPIO_Label=UI_SCL1
PB6.Mode=I2C
PB6.Signal=I2C1_SCL
PB7.GPIOParameters=GPIO_Label
PB7.GPIO_Label=UI_SDA1
PB7.Mode=I2C
PB7.Signal=I2C1_SDA
PB8.GPIOParameters=GPIO_Label
PB8.GPIO_Label=DISP_DC
PB8.Signal=GPIO_Output
PB9.GPIOParameters=GPIO_Label
PB9.GPIO_Label=DISP_RST
PB9.Signal=GPIO_Output
PC0.GPIOParameters=GPIO_PuPd,GPIO_Label
PC0.GPIO_Label=PTT_BTN
PC0.GPIO_PuPd=GPIO_PULLUP
PC0.Signal=GPIO_Input
PC1.GPIOParameters=GPIO_PuPd,GPIO_Label
PC1.GPIO_Label=PTT_AI_BTN
PC1.GPIO_PuPd=GPIO_PULLUP
PC1.Signal=GPIO_Input
PC10.GPIOParameters=GPIO_Label
PC10.GPIO_Label=I2S_BCLK
PC10.Mode=Full_Duplex_Slave
PC10.Signal=I2S3_CK
PC11.GPIOParameters=GPIO_Speed,GPIO_PuPd,GPIO_Label
PC11.GPIO_Label=UI_STAT
PC11.GPIO_PuPd=GPIO_PULLDOWN
PC11.GPIO_Speed=GPIO_SPEED_FREQ_MEDIUM
PC11.Signal=GPIO_Output
PC12.GPIOParameters=GPIO_PuPd,GPIO_Label
PC12.GPIO_Label=KB_ROW4
PC12.GPIO_PuPd=GPIO_PULLDOWN
PC12.Signal=GPIO_Input
PC13-ANTI_TAMP.GPIOParameters=GPIO_PuPd,GPIO_Label
PC13-ANTI_TAMP.GPIO_Label=KB_ROW5
PC13-ANTI_TAMP.GPIO_PuPd=GPIO_PULLDOWN
PC13-ANTI_TAMP.Signal=GPIO_Input
PC14-OSC32_IN.GPIOParameters=GPIO_PuPd,GPIO_Label
PC14-OSC32_IN.GPIO_Label=KB_ROW6
PC14-OSC32_IN.GPIO_PuPd=GPIO_PULLDOWN
PC14-OSC32_IN.Signal=GPIO_Input
PC15-OSC32_OUT.GPIOParameters=GPIO_Label
PC15-OSC32_OUT.GPIO_Label=KB_COL5
PC15-OSC32_OUT.Signal=GPIO_Output
PC2.GPIOParameters=GPIO_Label
PC2.GPIO_Label=UI_READY
PC2.Signal=GPIO_Output
PC3.GPIOParameters=GPIO_Label
PC3.GPIO_Label=NET_READY
PC3.Signal=GPXTI3
PC4.GPIOParameters=GPIO_PuPd,GPIO_Label
PC4.GPIO_Label=KB_ROW1
PC4.GPIO_PuPd=GPIO_PULLDOWN
PC4.Signal=GPIO_Input
PC5.GPIOParameters=GPIO_PuPd,GPIO_Label
PC5.GPIO_Label=KB_ROW2
PC5.GPIO_PuPd=GPIO_PULLDOWN
PC5.Signal=GPIO_Input
PC6.GPIOParameters=GPIO_Label
PC6.GPIO_Label=UI_LED_R
PC6.Signal=S_TIM3_CH1
PC7.GPIOParameters=GPIO_Label
PC7.GPIO_Label=UI_LED_G
PC7.Signal=S_TIM3_CH2
PC8.GPIOParameters=GPIO_Label
PC8.GPIO_Label=UI_LED_B
PC8.Signal=S_TIM3_CH3
PC9.GPIOParameters=GPIO_PuPd,GPIO_Label
PC9.GPIO_Label=KB_ROW3
PC9.GPIO_PuPd=GPIO_PULLDOWN
PC9.Signal=GPIO_Input
PD2.GPIOParameters=GPIO_Label
PD2.GPIO_Label=VOLUME_DOWN
PD2.Signal=GPIO_Input
PH0-OSC_IN.GPIOParameters=GPIO_Label
PH0-OSC_IN.GPIO_Label=MCLK
PH0-OSC_IN.Mode=HSE-External-Clock-Source
PH0-OSC_IN.Signal=RCC_OSC_IN
PH1-OSC_OUT.GPIOParameters=GPIO_Label
PH1-OSC_OUT.GPIO_Label=NC
PH1-OSC_OUT.Mode=HSE-External-Clock-Source
PH1-OSC_OUT.Signal=RCC_OSC_OUT
RCC.HSE_VALUE=12000000
RCC.SYSCLKFreq_VALUE=168000000
RCC.SYSCLKSource=RCC_SYSCLKSOURCE_PLLCLK
board=custom

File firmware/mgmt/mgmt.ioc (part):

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Mcu.Name=STM32F072C(8-B)Tx
Mcu.Package=LQFP48
Mcu.UserName=STM32F072C8Tx
PA0.GPIOParameters=GPIO_Label
PA0.GPIO_Label=CTS_NOT_NEEDED
PA0.Signal=GPIO_Input
PA1.GPIOParameters=GPIO_Label
PA1.GPIO_Label=RTS_NOT_NEEDED
PA1.Signal=GPIO_Input
PA10.GPIOParameters=GPIO_Label
PA10.GPIO_Label=USB_TX1_MGMT
PA10.Mode=Asynchronous
PA10.Signal=USART1_RX
PA11.Mode=Device
PA11.Signal=USB_DM
PA12.Mode=Device
PA12.Signal=USB_DP
PA13.Mode=Serial_Wire
PA13.Signal=SYS_SWDIO
PA14.Mode=Serial_Wire
PA14.Signal=SYS_SWCLK
PA15.GPIOParameters=GPIO_Label
PA15.GPIO_Label=UI_BOOT0
PA15.Signal=GPIO_Output
PA2.GPIOParameters=GPIO_Label
PA2.GPIO_Label=UI_RX1_MGMT
PA2.Mode=Asynchronous
PA2.Signal=USART2_TX
PA3.GPIOParameters=GPIO_Label
PA3.GPIO_Label=UI_TX1_MGMT
PA3.Mode=Asynchronous
PA3.Signal=USART2_RX
PA4.GPIOParameters=GPIO_Label
PA4.GPIO_Label=CHG_FB
PA4.Mode=IN4
PA4.Signal=ADC_IN4
PA5.GPIOParameters=GPIO_Label
PA5.GPIO_Label=RESERVED_DAC
PA5.Signal=COMP_DAC2_group
PA6.GPIOParameters=GPIO_Label
PA6.GPIO_Label=USB_CC1_DETECT
PA6.Mode=IN6
PA6.Signal=ADC_IN6
PA7.GPIOParameters=GPIO_Label
PA7.GPIO_Label=USB_CC2_DETECT
PA7.Mode=IN7
PA7.Signal=ADC_IN7
PA8.GPIOParameters=GPIO_Label
PA8.GPIO_Label=MCLK
PA8.Mode=Clock-out
PA8.Signal=RCC_MCO
PA9.GPIOParameters=GPIO_Label
PA9.GPIO_Label=USB_RX1_MGMT
PA9.Mode=Asynchronous
PA9.Signal=USART1_TX
PB0.GPIOParameters=GPIO_Label
PB0.GPIO_Label=BATTERY_MON
PB0.Mode=IN8
PB0.Signal=ADC_IN8
PB1.GPIOParameters=GPIO_Label
PB1.GPIO_Label=LEDA_B
PB1.Signal=S_TIM3_CH4
PB10.GPIOParameters=GPIO_Label
PB10.GPIO_Label=NET_RX1_MGMT
PB10.Mode=Asynchronous
PB10.Signal=USART3_TX
PB11.GPIOParameters=GPIO_Label
PB11.GPIO_Label=NET_TX1_MGMT
PB11.Mode=Asynchronous
PB11.Signal=USART3_RX
PB12.GPIOParameters=GPIO_Label
PB12.GPIO_Label=MGMT_DEBUG_2
PB12.Signal=GPIO_Output
PB3.GPIOParameters=GPIO_Label
PB3.GPIO_Label=UI_NRST
PB3.Signal=GPIO_Output
PB4.GPIOParameters=GPIO_Label
PB4.GPIO_Label=LEDA_G
PB4.Signal=S_TIM3_CH1
PB5.GPIOParameters=GPIO_Label
PB5.GPIO_Label=LEDA_R
PB5.Signal=S_TIM3_CH2
PB6.GPIOParameters=GPIO_Label
PB6.GPIO_Label=NET_BOOT
PB6.Signal=GPIO_Output
PB7.GPIOParameters=GPIO_Label
PB7.GPIO_Label=NET_STAT
PB7.Signal=GPIO_Input
PB8.GPIOParameters=GPIO_Label
PB8.GPIO_Label=UI_BOOT1
PB8.Signal=GPIO_Output
PB9.GPIOParameters=GPIO_Label
PB9.GPIO_Label=UI_STAT
PB9.Signal=GPIO_Input
PC13.GPIOParameters=GPIO_Label
PC13.GPIO_Label=NET_NRST
PC13.Signal=GPIO_Input
PC14-OSC32_IN.GPIOParameters=GPIO_Label
PC14-OSC32_IN.GPIO_Label=MGMT_DEBUG_1
PC14-OSC32_IN.Signal=GPIO_Output
PF0-OSC_IN.Mode=HSE-External-Oscillator
PF0-OSC_IN.Signal=RCC_OSC_IN
PF1-OSC_OUT.Mode=HSE-External-Oscillator
PF1-OSC_OUT.Signal=RCC_OSC_OUT
RCC.HSE_VALUE=16000000
RCC.SYSCLKFreq_VALUE=48000000
RCC.SYSCLKSource=RCC_SYSCLKSOURCE_PLLCLK
board=custom

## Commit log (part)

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2026-05-31 update filter cap values
2026-05-31 update schematic date
2026-06-01 Added jlcpcb part numbers to the capacitors, to R83, and the ferrite beads
2026-06-01 Changed R83's part number to be a 4R7 instead of 47K. Changed the footprint to match
2026-06-01 Fixed error with part number in C59
2026-06-01 Add missing jlcpcb part for C53
2026-06-02 update caps for ldo, flip jp3 to default to vsys, update wm8960 and ch340c part, change holes to solder pads 2mm (refs #497, #546, #542, #472, #590)
2026-06-02 Added 33k terminating resistor to LIN1 input side (refs #531)
2026-06-04 update schematic to have mic design for reference
2026-06-04 start RF filters
2026-06-04 add mic circuit for reference
2026-06-04 Finish audio section reqdesign
2026-06-04 add text version of datasheets for AI to read
2026-06-05 address PR review
2026-06-05 Update side buttons, 3.5mm jack, and 2.5mm jack footprints to match their datasheets
2026-06-06 Fixed ERC errors and warnings, and fixed update pcb warnings
2026-06-08 Fix ERC and DRC. Filled in more ungrounded areas
2026-06-08 Changed esp32 part number to ESP32-S3-WMROOM-1U-N8R2
2026-06-08 Added some notes to indicate that the esp32 is the external antenna version
2026-06-08 Update titles and dates
2026-06-08 Change EV18 WM8960 back to original part for assembly. Change 0R1 resistors to a different part number. Change TP to Exclude from BOM
2026-06-08 Initial ev19 commit
2026-06-08 Convert to kicad10
2026-06-09 Moved mgmt, usb, and power to their own sheets
2026-06-10 Added a sheet for the dev board and wired up the remaining connections
2026-06-10 Add a csv that details the nubmer of extended parts
2026-06-11 add 10k resistor to 3.5mm tip (refs #528)
2026-06-11 Switched current sense resistor to C25334 (refs #555)
2026-06-11 Cleaned up a mgmt nrst, leds, ptt, and volume schematics
2026-06-12 Added more rules, to adhere to what jlcpcb expects
2026-06-15 Added more DRC rules (refs #499)
2026-06-15 Update the footprint for ESP32-S3 and TPS63060 to be kicad built-in footprint (refs #501)
2026-06-16 Add BBQ10 keyboard and screen connectors (refs #421)
2026-06-16 Update keyboard symbol to have jlcpcb part number and offset
2026-06-16 Changed PJ-242 to built-in symbol. Updated PJ-242 footprint to match symbol. (refs #558)
2026-06-17 Added solder jumper to a resistor to the mgmt dac to control iset (refs #169)
2026-06-17 Added ES8311 to schematic, but we are undecided on if we should use it
2026-06-18 added audio schematic page
2026-06-19 Moved 3 sections to their own sheets and wired them together
2026-06-19 Audio codec with ES8311 design (refs #554)
2026-06-19 Put both kb led pins onto the same pwm pin, and added a mosfet so we have space for a headphone detect
2026-06-20 Added headphone jack detect WIP (refs #447)
2026-06-22 Added RC filter to mic detect plugin
2026-06-22 Upgrade to kicad10
2026-06-23 Added missing footprints, used kicad10 wizard tool to design them, designed starting point of the board layout
2026-06-24 Fixed a couple mistakes on the schematic, got general power layout of the hactar designed, finding layout for audio section
2026-06-29 Changed from using reinterpret cast to AsBytes to fix crash
2026-06-29 Update binaries from Nightly build
2026-06-30 Added blaster functionality to net's commands
